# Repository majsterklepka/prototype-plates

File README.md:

# prototype-plates
Prototype Plates Projects for Electronics Engineers

Well..., well! Here you are! Of course, here are the Projects, My Projects, all about electronics. Especially for You, and Me.

All the attached projects concern an issue called the mechanical construction of electronic systems. I will not hide that I put here projects created with me in mind and by the way, maybe someone will find them useful.

In the construction of prototypes ...? Prototype board and contact plate. Here you will see projects specially prepared for the construction of prototypes.

## Credits
 
Author: SQ7EQE op Paweł

blog: [majsterklepka.github.io](https://majsterklepka.github.io/ "Author Personal Blog")

License:

- GNU GPLv3
- GNU FDL-1.3
- CC-BY-SA, in some reason

- - -

Have fun and share that projects with friends! Feel free, and do what your heart told you!

Ups! I will be forgotten! Remember the Author & carefully read licenses contents!

**© Paweł Sobótka, 2019 all rights reserved**

_Msc. Paweł Sobótka (SQ7EQE)_  
Author

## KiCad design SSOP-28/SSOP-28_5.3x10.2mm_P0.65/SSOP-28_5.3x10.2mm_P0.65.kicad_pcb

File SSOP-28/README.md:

# Package SSOP-28
prototype boards

hi there!

Proposal for today: the prototype board! Below I have shown the picture of that project:

All project files are included in folders created for separate projects. I have attached the mechanical drawings with dimensions too, see **dxf/** folder. These projects you can make at home, first you must prepare 2D view of PCB Layout by export to SVG file Front layer of PCB in b&w, make an PNG picture at 300 dpi and print it at your printer. Especially I have designed one side PCB, which will help you to make selected project or both projects by yourself.

# Credits

Projects are licensed under terms of two licenses:

- GNU GPLv3
- GNU FDL-1.3

Documentation are made with KiCad & LibreCad, the Open Source CAD software.

Feel free, share these projects with friends!

See later!

_Msc. Paweł Sobótka (SQ7EQE)_

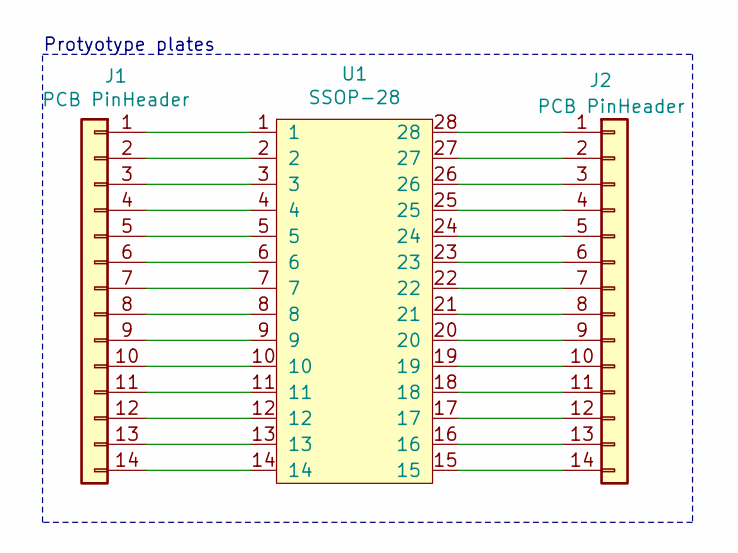
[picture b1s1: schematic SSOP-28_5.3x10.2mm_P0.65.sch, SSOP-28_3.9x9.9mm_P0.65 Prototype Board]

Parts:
J1, J2: PCB PinHeader; PinHeader_1x14_P2.54mm_Vertical
U1: SSOP-28; SSOP-28_5.3x10.2mm_P0.65mm

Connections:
unnamed: J1.1, U1.1
unnamed: J1.2, U1.2
unnamed: J1.3, U1.3
unnamed: J1.4, U1.4
unnamed: J1.5, U1.5
unnamed: J1.6, U1.6
unnamed: J1.7, U1.7
unnamed: J1.8, U1.8
unnamed: J1.9, U1.9
unnamed: J1.10, U1.10
unnamed: J1.11, U1.11
unnamed: J1.12, U1.12
unnamed: J1.13, U1.13
unnamed: J1.14, U1.14
unnamed: J2.1, U1.28
unnamed: J2.2, U1.27
unnamed: J2.3, U1.26
unnamed: J2.4, U1.25
unnamed: J2.5, U1.24
unnamed: J2.6, U1.23
unnamed: J2.7, U1.22
unnamed: J2.8, U1.21
unnamed: J2.9, U1.20
unnamed: J2.10, U1.19
unnamed: J2.11, U1.18
unnamed: J2.12, U1.17
unnamed: J2.13, U1.16
unnamed: J2.14, U1.15

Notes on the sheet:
Protyotype plates

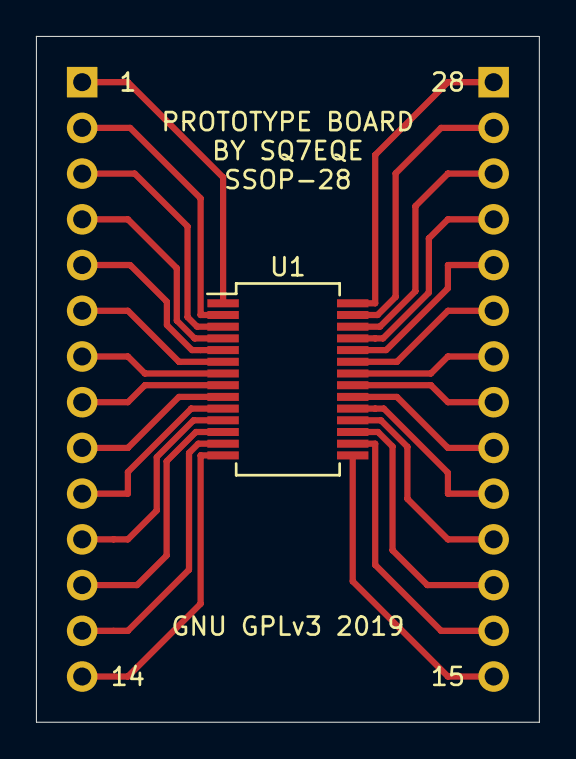
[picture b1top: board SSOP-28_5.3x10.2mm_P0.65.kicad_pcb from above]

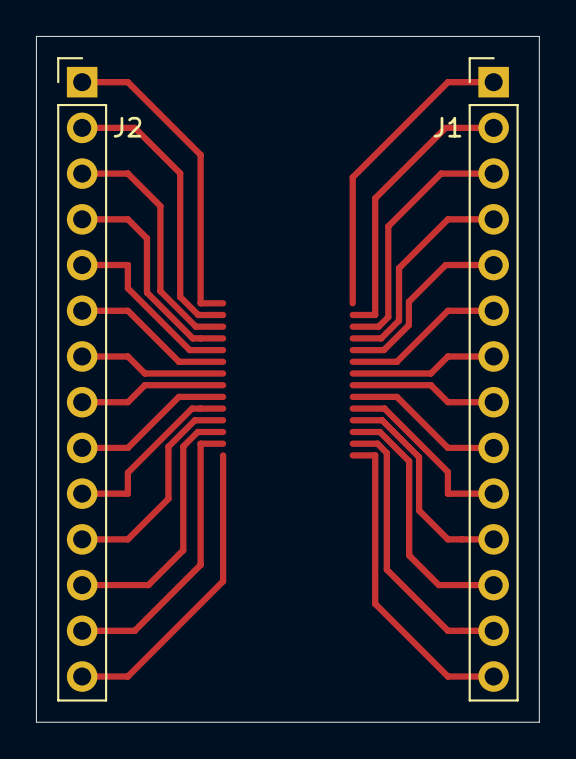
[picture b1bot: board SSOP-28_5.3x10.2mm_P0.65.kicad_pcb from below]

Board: 2 copper layers, 27.9 x 38.1 mm, 3 parts (2 on the bottom side), 28 nets.

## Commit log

2019-11-24 update: I have updated README file
    I have add body to file,
2019-11-24 update: I have attached FDL-1.3 license file!
2019-11-27 update: new projects are ready
2019-11-27 update: I have repair path to the picture
2019-11-27 update: I have repair path to picture
2019-11-28 update: redrawn
2020-02-20 update: new pcb Gerber files
2020-02-20 update: new files
2020-02-20 update: fixes path(s)wq
2020-02-20 update: image regeneration
2020-02-21 update: new Gerber files
2020-02-21 update: fixe title
2020-02-21 update: repair Gerber files
2020-02-21 update: new file
2020-02-21 update: new file with mechanical drawing
2020-02-21 update: modified file
2020-02-29 update: update picture
2020-02-29 update: add new project file
2020-10-05 new pcb project
2020-10-05 add file
2020-10-05 new file
    I have included picture with layout of PCB
2020-10-05 file updated

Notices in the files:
SSOP-28/SSOP-28_5.3x10.2mm_P0.65/SSOP-28_5.3x10.2mm_P0.65.kicad_pcb:
GNU GPLv3 2019
